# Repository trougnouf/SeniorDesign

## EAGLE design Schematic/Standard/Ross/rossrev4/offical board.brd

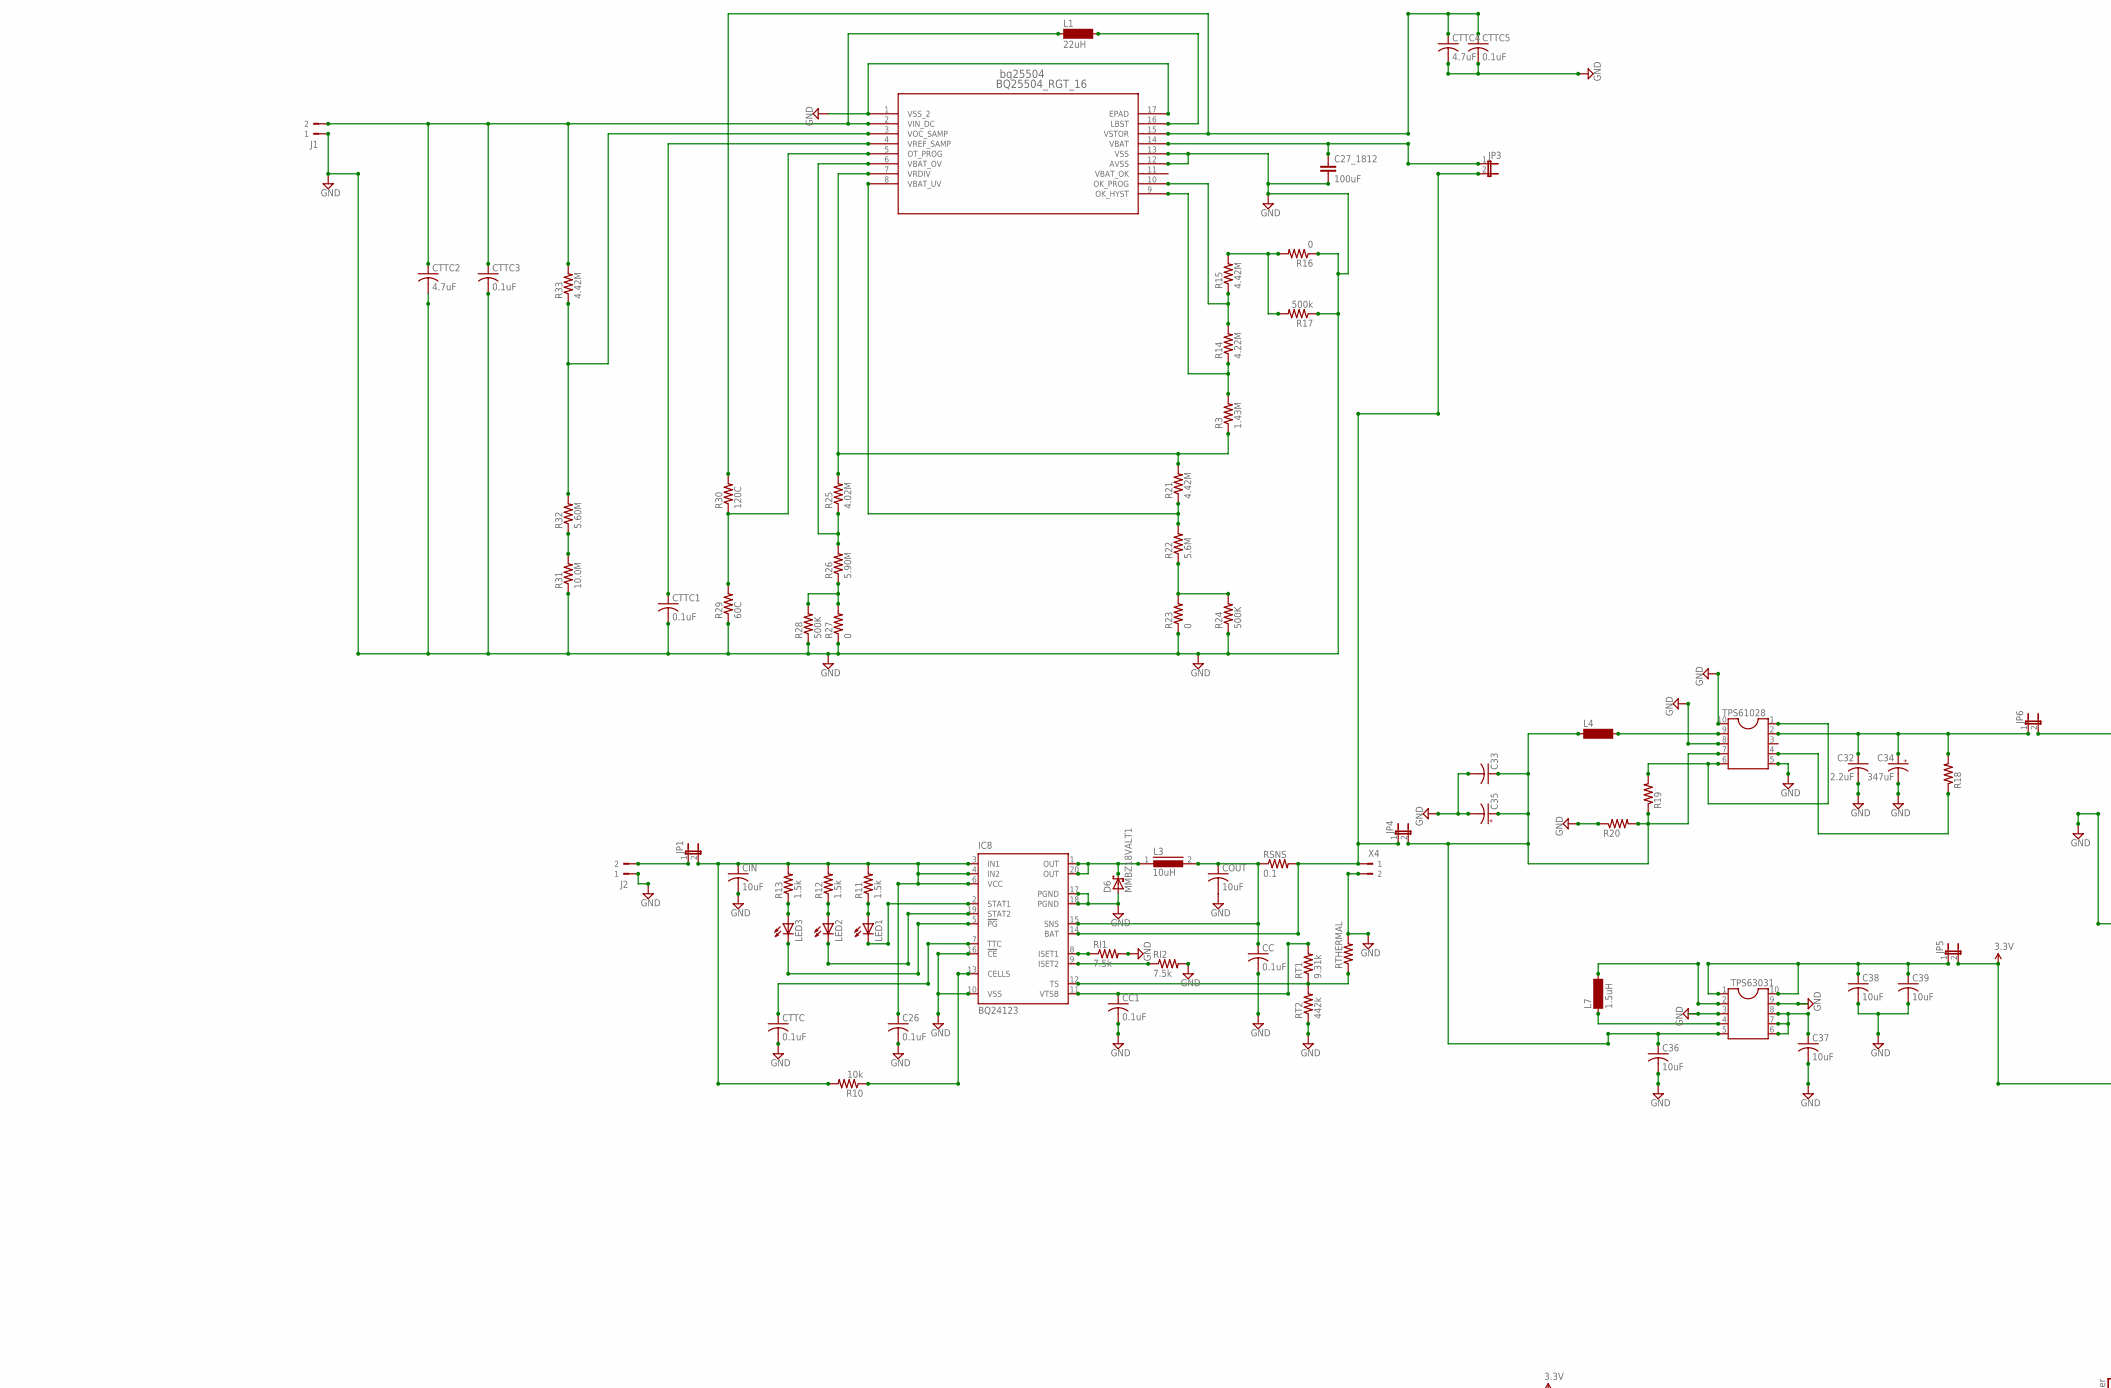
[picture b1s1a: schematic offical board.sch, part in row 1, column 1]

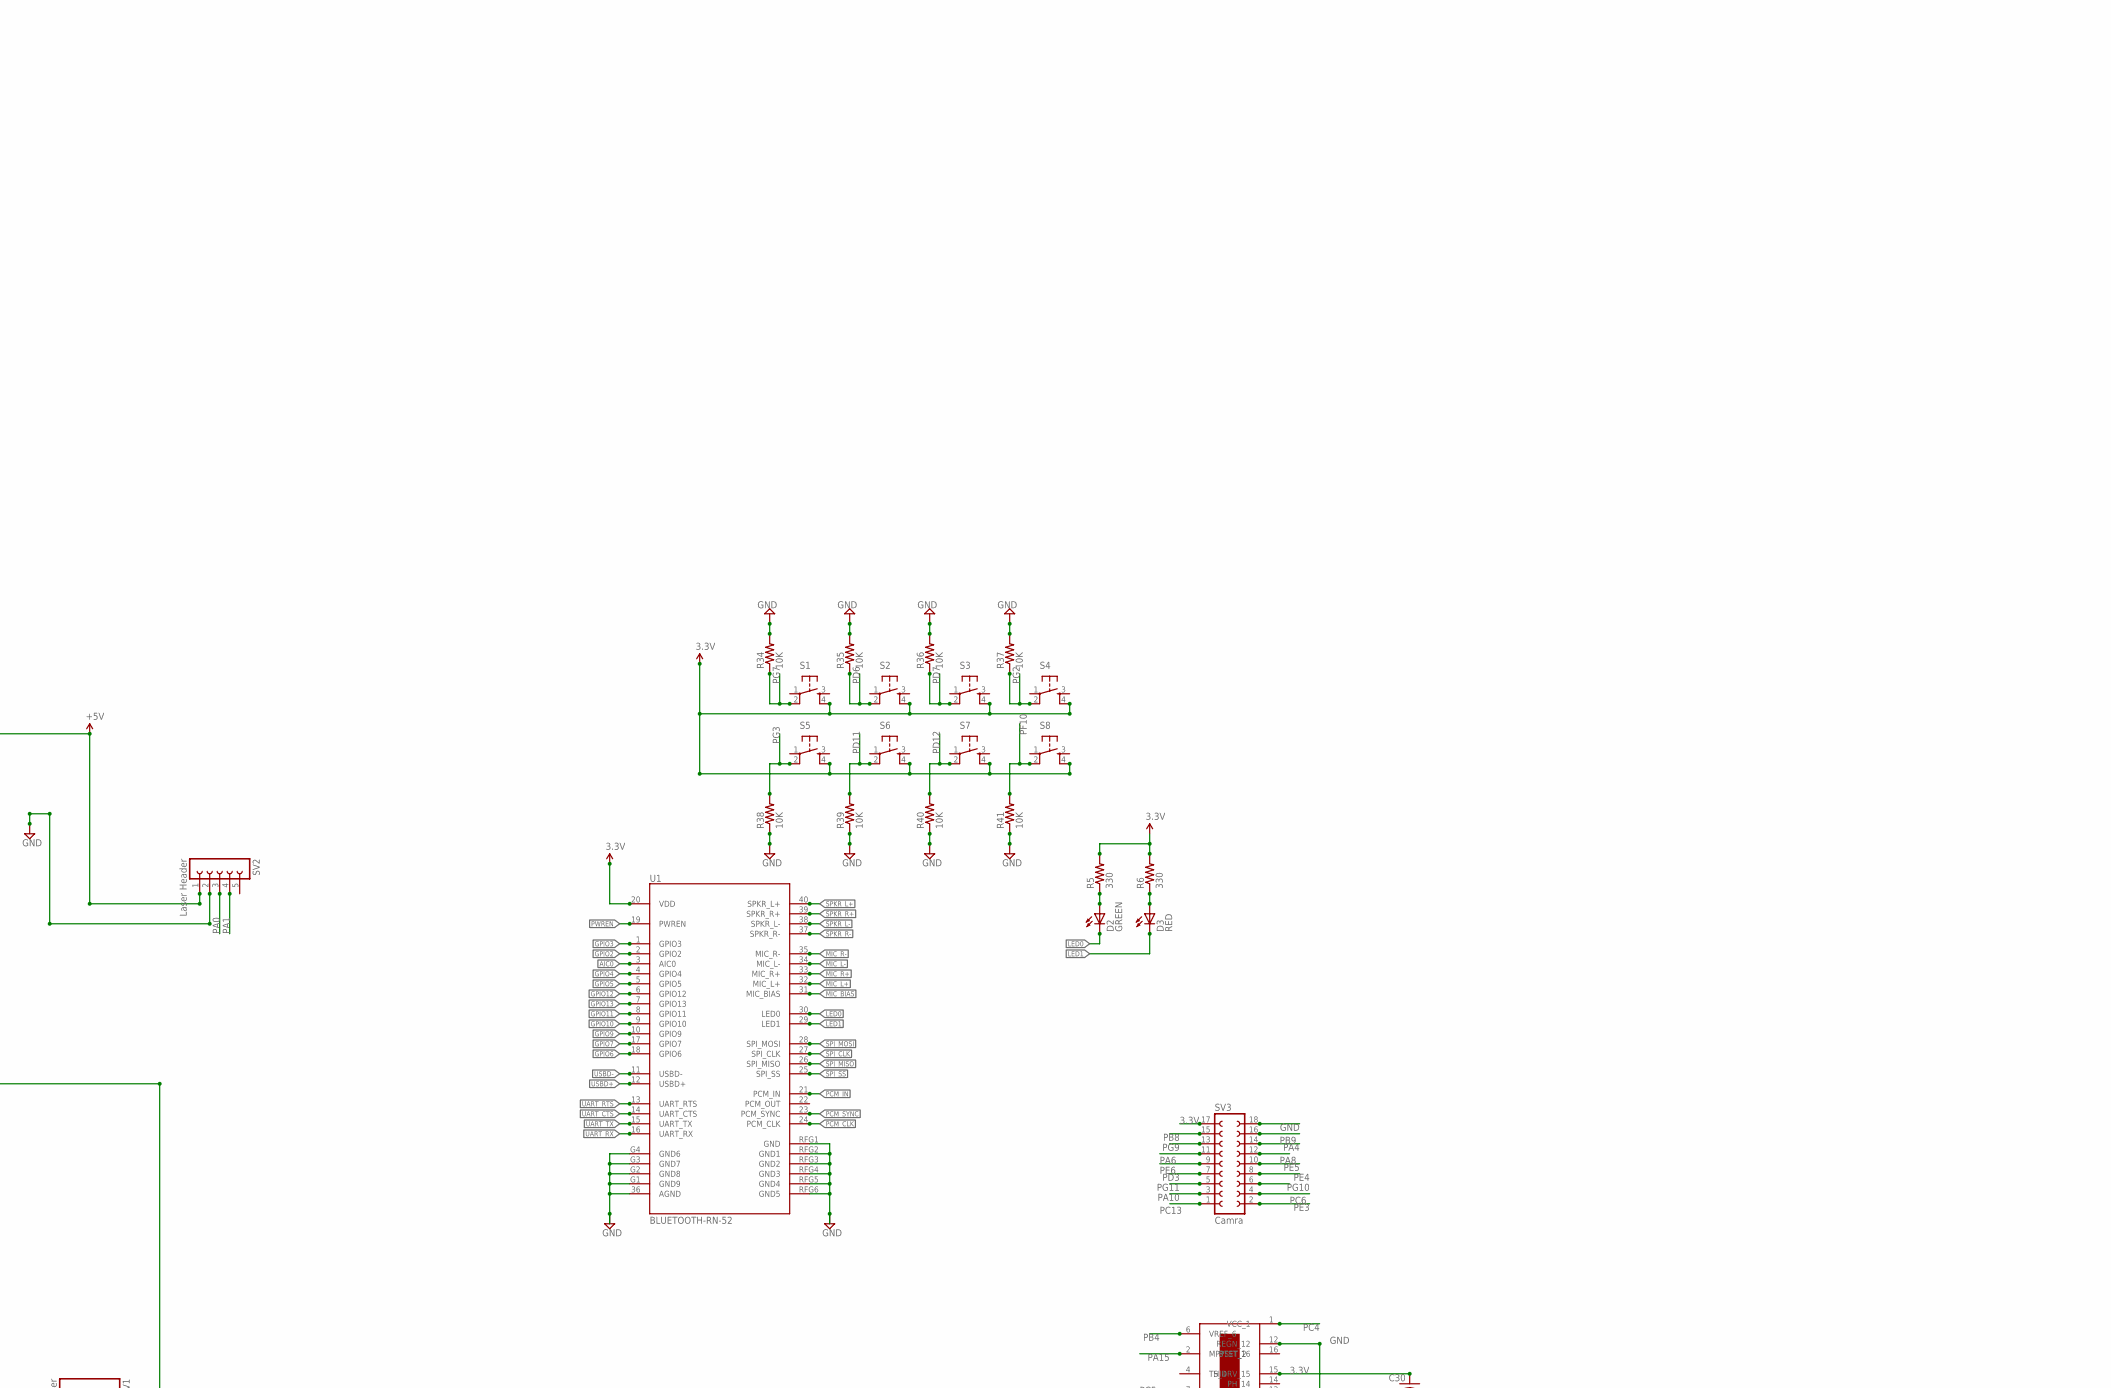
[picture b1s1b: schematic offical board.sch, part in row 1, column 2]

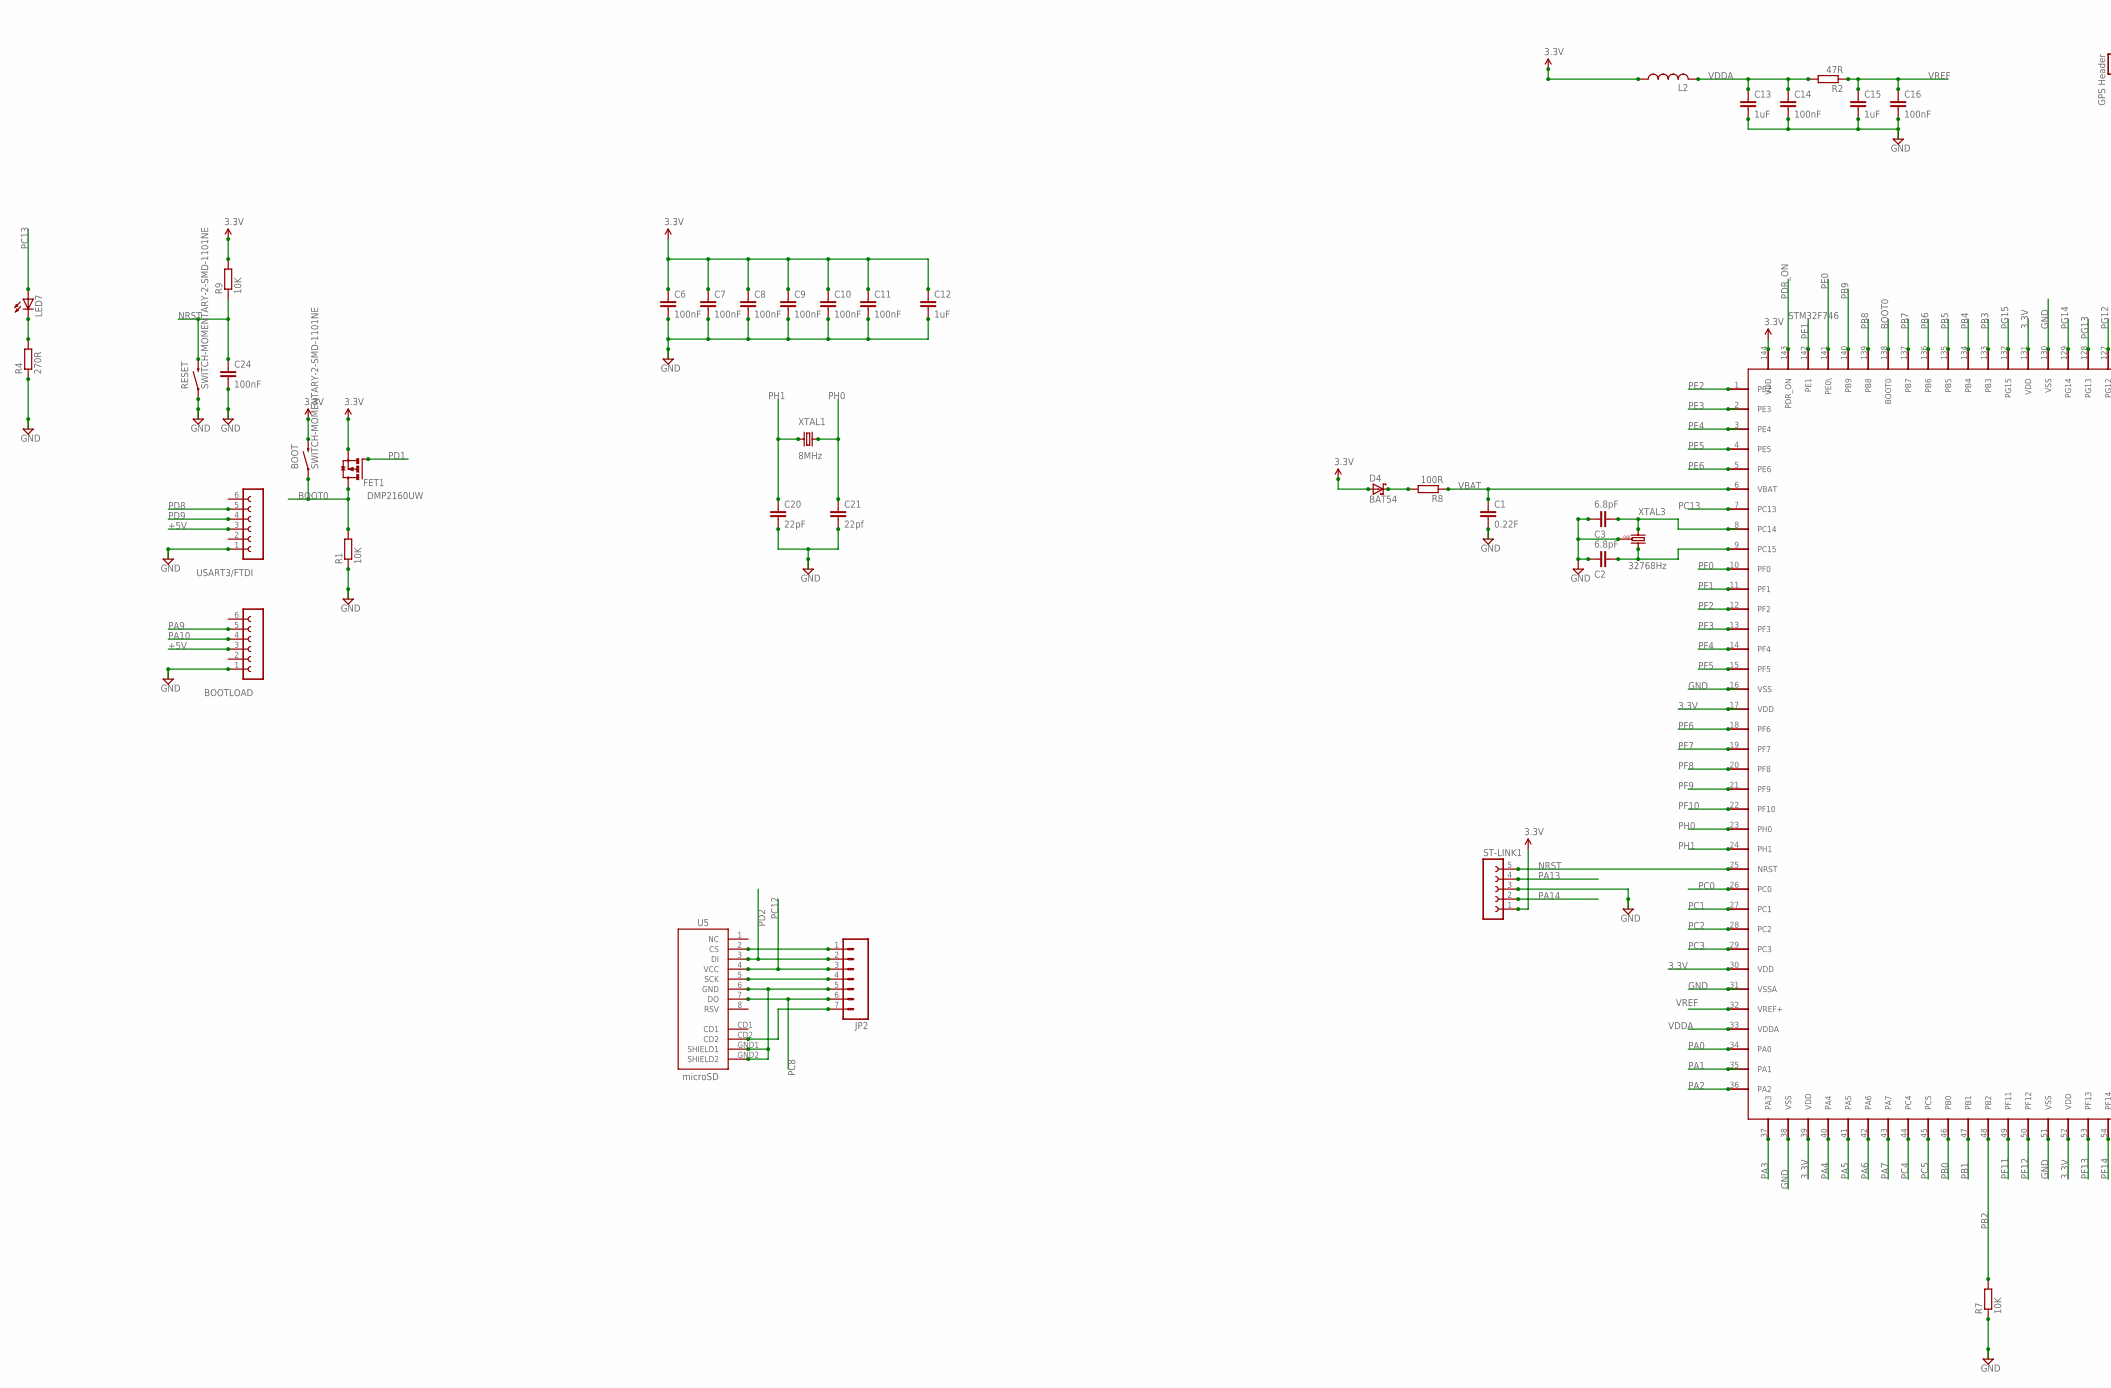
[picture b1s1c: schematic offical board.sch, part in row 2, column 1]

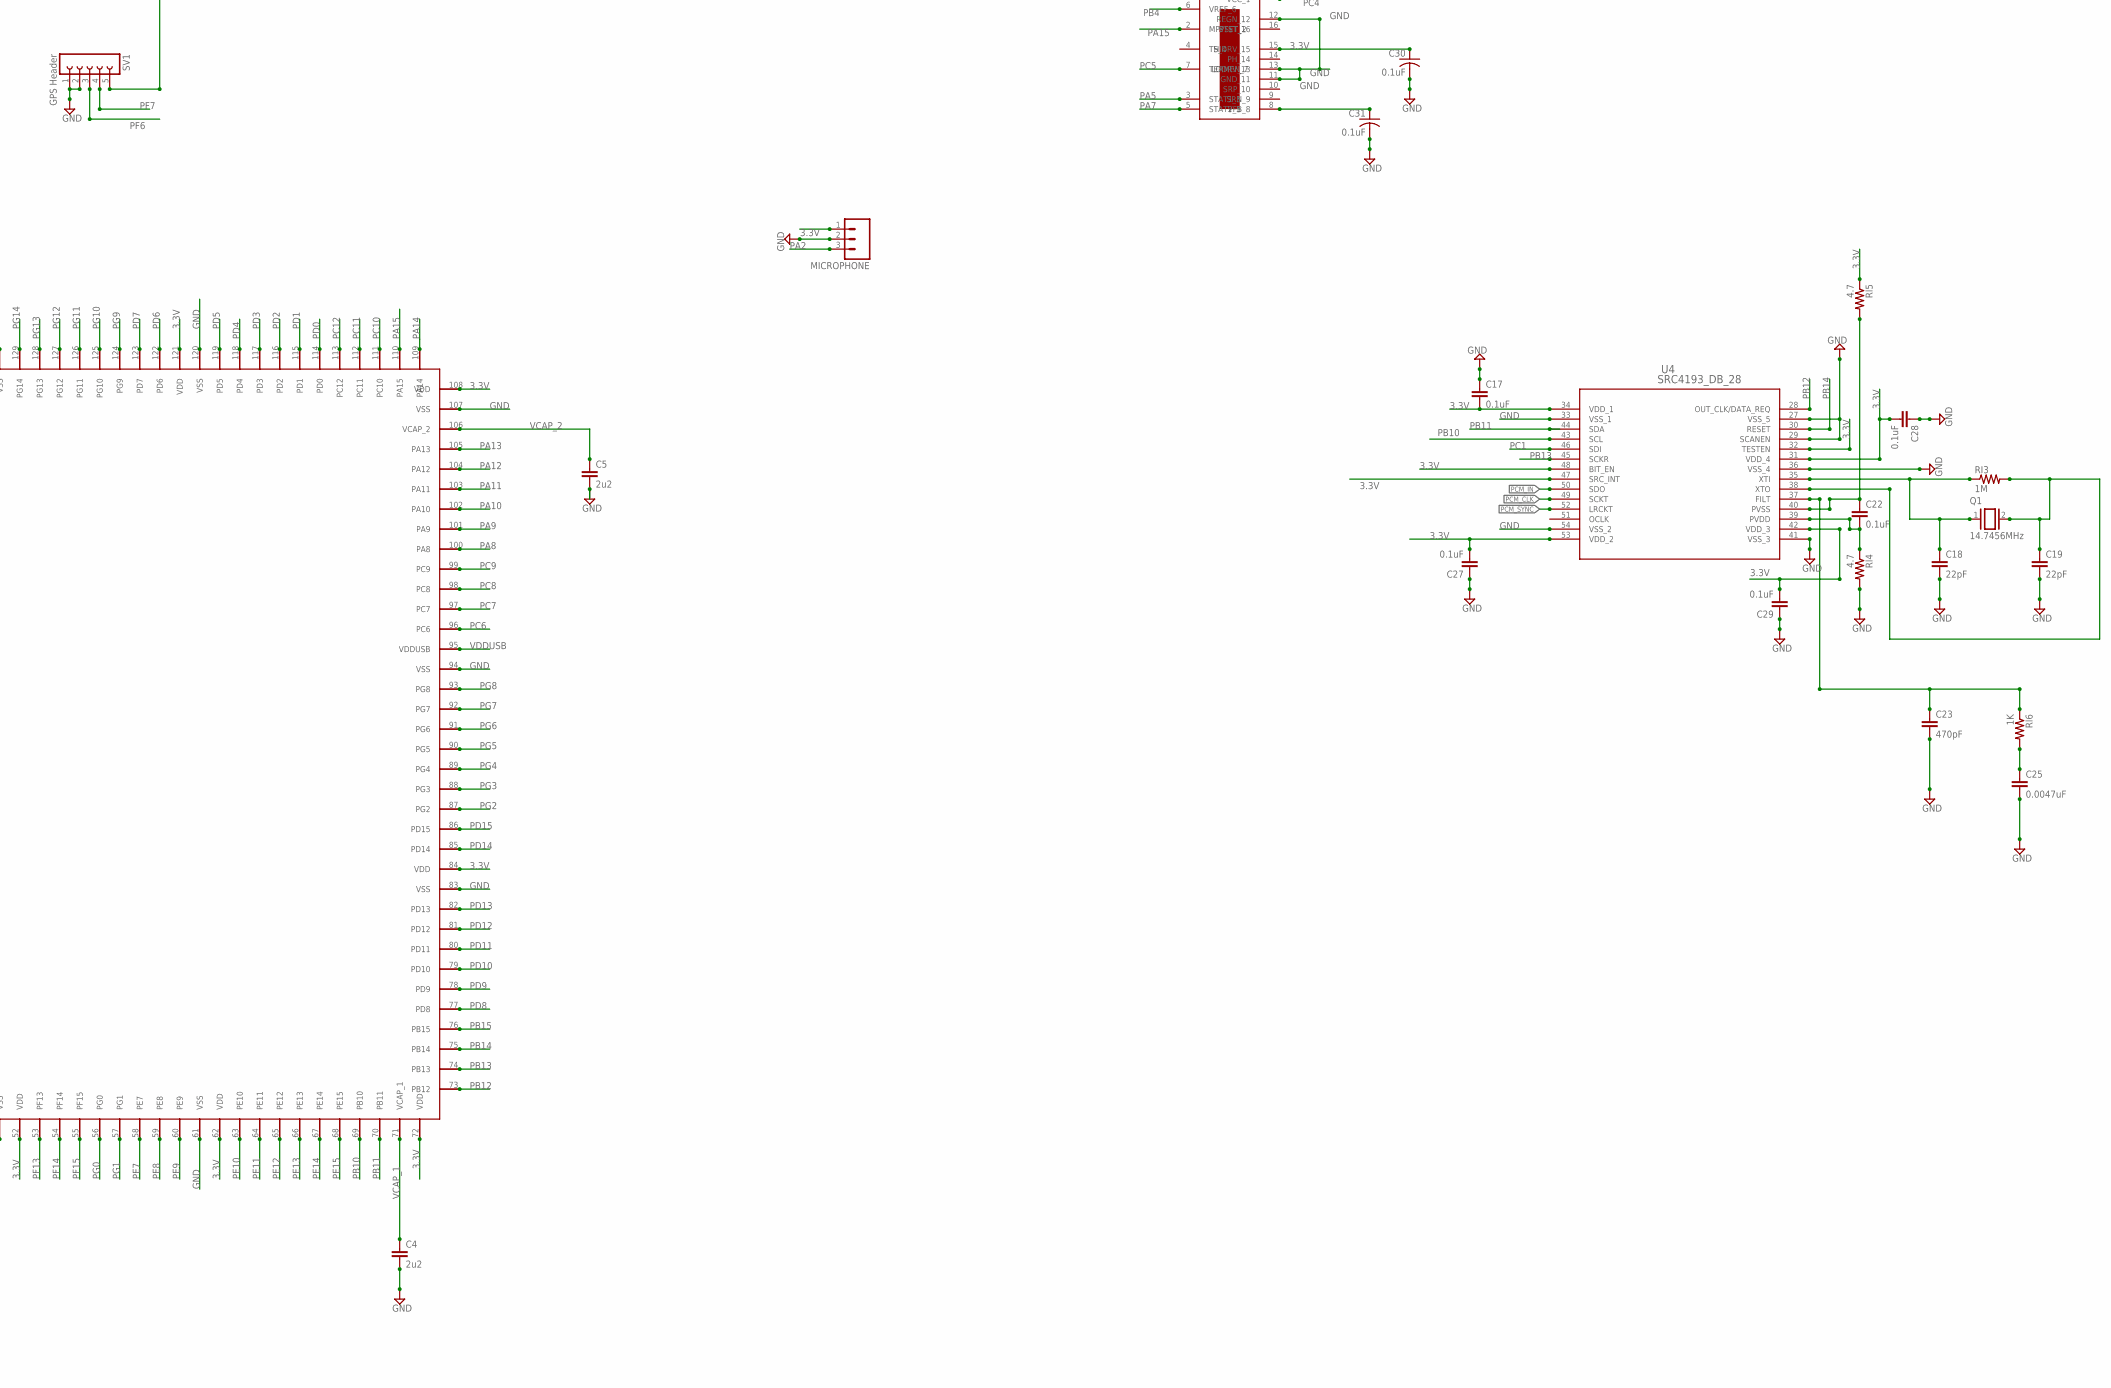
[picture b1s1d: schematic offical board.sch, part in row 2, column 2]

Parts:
BOOT: SWITCH-MOMENTARY-2-SMD-1101NE; TACTILE-SWITCH-1101NE
BOOTLOAD: FE06-1; FE06
C1: 0.22F; C5B5
C2, C3: 6.8pF; C0603
C4, C5: 2u2; C0603
C6, C7, C8, C9, C10, C11, C14, C16, C24: 100nF; C0603
C12, C13, C15: 1uF; C0603
C17, C22, C27, C28, C29, C30, C31: 0.1uF; C0603
C18, C19, C20: 22pF; C0603
C21: 22pf; C0603
C23: 470pF; C0603
C25: 0.0047uF; C0603
C26: 0.1uF; C0805
C27_1812: 100uF; C1812
C32: 2.2uF; C0603
C33: C-USC0603; C0603
C34: 347uF; 150CLZ-0810
C35: CPOL-US150CLZ-0810; 150CLZ-0810
C36, C37, C38, C39: 10uF; C0603
CC, CC1: 0.1uF; C0805
CIN: 10uF; C0805
COUT: 10uF; C0805
CTTC, CTTC1, CTTC3, CTTC5: 0.1uF; C0805
CTTC2, CTTC4: 4.7uF; C0805
D2: GREEN; LED-0603
D3: RED; LED-0603
D4: BAT54; SOT23
D6: MMBZ18VALT1; C4111-15
FET1: DMP2160UW; SUPER-SOT3
IC8: BQ24123; QFN20_3,5X4,5
J1, J2: 90-2
JP1, JP3, JP4, JP5, JP6: JP1E; JP1
JP2: M07; 1X07
L1: 22uH; SM-1206
L2: RCL_L-USL0603; RCL_L0603
L3: 10uH; DR73
L4: SM-1206
L7: 1.5uH; SM-1206
LED1, LED2, LED3: SFH482
LED7: LEDCHIP-LED0603; CHIP-LED0603
MICROPHONE: M03PTH; 1X03
Q1: 14.7456MHz; QS
R1, R7, R9: 10K; R0603
R2: 47R; R0603
R3: 1.43M; R0805
R4: 270R; R0603
R5, R6: 330; 0603-RES
R8: 100R; R0603
R10: 10k; R0805
R11, R12, R13: 1.5k; R0805
R14: 4.22M; R0805
R15, R21, R33: 4.42M; R0805
R16, R23, R27: 0; R0805
R17: 500k; R0805
R18, R19, R20: R-US_R0603; R0603
R22: 5.6M; R0805
R24, R28: 500K; R0805
R25: 4.02M; R0805
R26: 5.90M; R0805
R29: 60C; R0805
R30: 120C; R0805
R31: 10.0M; R0805
R32: 5.60M; R0805
R34, R35, R36, R37, R38, R39, R40, R41: 10K; 0603-RES
RESET: SWITCH-MOMENTARY-2-SMD-1101NE; TACTILE-SWITCH-1101NE
RI1, RI2: 7.5k; R0805
RI3: 1M; R0805
RI4, RI5: 4.7; R0805
RI6: 1K; R0805
RSNS: 0.1; R1206
RT1: 9.31k; R0805
RT2: 442k; R0805
RTHERMAL: R-US_R0805; R0805
S1, S2, S3, S4, S5, S6, S7, S8: TAC_SWITCHSMD; TACTILE_SWITCH_SMD
ST-LINK1: FE05-1
SV1: GPS Header; FE05-1
SV2: Laser Header; FE05-1
SV3: Camra; FE09-2
TPS61028, TPS63031: DIL10
U1: BLUETOOTH-RN-52; RN-52
U3: BQ25504_RGT_16; RGT16_1P7X1P7
U4: SRC4193_DB_28; DB28
U5: microSD; MICRO-SD-SOCKET-PP
U$1: STM32F746; QFN144
U$2: QFN16
USART3/FTDI: FE06-1; FE06
X4: 90-2
XTAL1: 8MHz; HC49U-V
XTAL3: 32768Hz; CRYSTAL_TC26H_3_REPAIR_SMD_SMALL_PITCH

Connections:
3.3V: BOOT.P$2 (2), C6.1, C7.1, C8.1, C9.1, C10.1, C11.1, C12.1, C17.2, C27.2, C28.2, C29.2, C30.1, D4.1 (A), FET1.2 (S), JP5.2, L2.1, MICROPHONE.1, R5.2, R6.2, R9.2, RI5.1, S1.4, S2.4, S3.4, S4.4, S5.4, S6.4, S7.4, S8.4, ST-LINK1.1, SV1.5, SV3.17, U1.20 (VDD), U4.31 (VDD_4), U4.32 (TESTEN), U4.34 (VDD_1), U4.42 (VDD_3), U4.47 (SRC_INT), U4.48 (BIT_EN), U4.53 (VDD_2), U$1.17 (VDD), U$1.30 (VDD), U$1.39 (VDD), U$1.52 (VDD), U$1.62 (VDD), U$1.72 (VDD), U$1.84 (VDD), U$1.108 (VDD), U$1.121 (VDD), U$1.131 (VDD), U$1.144 (VDD), U$2.15 (HIDRV_15)
+5V: BOOTLOAD.3, JP6.2, SV2.1, USART3/FTDI.3
AIC0: U1.3 (AIC0)
BOOT0: BOOT.P$1 (1), FET1.3 (D), R1.2, U$1.138 (BOOT0)
CD2: JP2.7, U5.CD2
CS1: JP2.1, U5.2 (CS)
GND: BOOTLOAD.1, C1.2, C2.2, C3.2, C4.2, C5.2, C6.2, C7.2, C8.2, C9.2, C10.2, C11.2, C12.2, C13.2, C14.2, C15.2, C16.2, C17.1, C18.2, C19.2, C20.2, C21.2, C23.2, C24.2, C25.2, C26.2, C27.1, C27_1812.2, C28.1, C29.1, C30.2, C31.2, C32.2, C33.2, C34.-, C35.-, C36.2, C37.2, C38.2, C39.2, CC.2, CC1.2, CIN.2, COUT.2, CTTC.2, CTTC1.2, CTTC2.2, CTTC3.2, CTTC4.2, CTTC5.2, D6.A, IC8.10 (VSS), IC8.16 (!CE), IC8.17 (PGND), IC8.18 (PGND), J1.1, J2.1, MICROPHONE.2, R1.1, R4.1, R7.1, R16.1, R17.1, R20.1, R23.1, R24.1, R27.1, R28.1, R29.1, R31.1, R34.2, R35.2, R36.2, R37.2, R38.1, R39.1, R40.1, R41.1, RESET.P$1 (1), RI1.2, RI2.2, RI4.2, RT2.1, RTHERMAL.2, ST-LINK1.3, SV1.1, SV1.2, SV2.2, SV3.18, TPS61028.5, TPS61028.8, TPS61028.10, TPS63031.3, TPS63031.9, U1.36 (AGND), U1.G1 (GND9), U1.G2 (GND8), U1.G3 (GND7), U1.G4 (GND6), U1.RFG1 (GND), U1.RFG2 (GND1), U1.RFG3 (GND2), U1.RFG4 (GND3), U1.RFG5 (GND4), U1.RFG6 (GND5), U3.1 (VSS_2), U3.12 (AVSS), U3.13 (VSS), U3.17 (EPAD), U4.27 (VSS_5), U4.29 (SCANEN), U4.33 (VSS_1), U4.36 (VSS_4), U4.41 (VSS_3), U4.54 (VSS_2), U$1.16 (VSS), U$1.31 (VSSA), U$1.38 (VSS), U$1.51 (VSS), U$1.61 (VSS), U$1.83 (VSS), U$1.94 (VSS), U$1.107 (VSS), U$1.120 (VSS), U$1.130 (VSS), U$2.11 (GND_11), U$2.12 (REGN_12), U$2.13 (LODRV_13), USART3/FTDI.1, X4.2, XTAL3.GND
GND2: JP2.5, U5.6 (GND), U5.GND1 (SHIELD1), U5.GND2 (SHIELD2)
GPIO2: U1.2 (GPIO2)
GPIO3: U1.1 (GPIO3)
GPIO4: U1.4 (GPIO4)
GPIO5: U1.5 (GPIO5)
GPIO6: U1.18 (GPIO6)
GPIO7: U1.17 (GPIO7)
GPIO9: U1.10 (GPIO9)
GPIO10: U1.9 (GPIO10)
GPIO11: U1.8 (GPIO11)
GPIO12: U1.6 (GPIO12)
GPIO13: U1.7 (GPIO13)
LED0: D2.C, U1.30 (LED0)
LED1: D3.C, U1.29 (LED1)
MIC_BIAS: U1.31 (MIC_BIAS)
MIC_L+: U1.32 (MIC_L+)
MIC_L-: U1.34 (MIC_L-)
MIC_R+: U1.33 (MIC_R+)
MIC_R-: U1.35 (MIC_R-)
unnamed: D3.A, R6.1
unnamed: D2.A, R5.1
unnamed: D4.3 (C), R8.2
unnamed: C33.1, C35.+, C36.1, JP4.2, L4.1, R19.1, R20.2, TPS61028.7, TPS63031.5
unnamed: C18.1, Q1.1, RI3.1, U4.35 (XTI)
unnamed: D6.C, IC8.1 (OUT), IC8.20 (OUT), L3.1
unnamed: C23.1, RI6.1, U4.37 (FILT)
unnamed: J2.2, JP1.1
unnamed: C19.1, Q1.2, RI3.2, U4.38 (XTO)
unnamed: CTTC2.1, CTTC3.1, J1.2, L1.1, R33.2, U3.2 (VIN_DC)
unnamed: C25.1, RI6.2
unnamed: CC.1, COUT.1, IC8.15 (SNS), L3.2, RSNS.1
unnamed: C22.2, RI4.1, U4.39 (PVDD)
unnamed: C22.1, RI5.2, U4.40 (PVSS)
unnamed: C27_1812.1, JP3.1, U3.14 (VBAT)
unnamed: CTTC4.1, CTTC5.1, R30.2, U3.15 (VSTOR)
unnamed: IC8.14 (BAT), JP3.2, JP4.1, RSNS.2, X4.1
unnamed: IC8.8 (ISET1), RI1.1
unnamed: R14.2, R15.1, U3.10 (OK_PROG)
unnamed: R3.2, R14.1, U3.9 (OK_HYST)
unnamed: IC8.9 (ISET2), RI2.1
unnamed: IC8.12 (TS), RT1.1, RT2.2, RTHERMAL.1
unnamed: CC1.1, IC8.11 (VTSB), RT1.2
unnamed: LED3.A, R13.1
unnamed: LED2.A, R12.1
unnamed: LED1.A, R11.1
unnamed: IC8.2 (STAT1), LED1.K (C)
unnamed: IC8.19 (STAT2), LED2.K (C)
unnamed: IC8.5 (!PG), LED3.K (C)
unnamed: CTTC.1, IC8.7 (TTC)
unnamed: IC8.13 (CELLS), R10.1
unnamed: R15.2, R16.2, R17.2
unnamed: R3.1, R21.2, R25.2, U3.7 (VRDIV)
unnamed: R21.1, R22.2, U3.8 (VBAT_UV)
unnamed: R22.1, R23.2, R24.2
unnamed: C38.1, C39.1, JP5.1, TPS63031.1, TPS63031.10
unnamed: C26.1, CIN.1, IC8.3 (IN1), IC8.4 (IN2), IC8.6 (VCC), JP1.2, R10.2, R11.2, R12.2, R13.2
unnamed: C31.1, U$2.8 (VFB_8)
unnamed: L1.2, U3.16 (LBST)
unnamed: R25.1, R26.2, U3.6 (VBAT_OV)
unnamed: R26.1, R27.2, R28.2
unnamed: CTTC1.1, U3.4 (VREF_SAMP)
unnamed: C32.1, C34.+, JP6.1, R18.2, TPS61028.2
unnamed: R18.1, TPS61028.4
unnamed: R19.2, TPS61028.1, TPS61028.6
unnamed: R29.2, R30.1, U3.5 (OT_PROG)
unnamed: L4.2, TPS61028.9
unnamed: L7.2, TPS63031.2
unnamed: L7.1, TPS63031.4
unnamed: C37.1, TPS63031.6, TPS63031.7, TPS63031.8
unnamed: R31.2, R32.1
unnamed: R32.2, R33.1, U3.3 (VOC_SAMP)
unnamed: LED7.C, R4.2
NRST: C24.1, R9.1, RESET.P$2 (2), ST-LINK1.5, U$1.25 (NRST)
PA0: SV2.3, U$1.34 (PA0)
PA1: SV2.4, U$1.35 (PA1)
PA2: MICROPHONE.3, U$1.36 (PA2)
PA3: U$1.37 (PA3)
PA4: SV3.14, U$1.40 (PA4)
PA5: U$1.41 (PA5), U$2.3 (STAT1_3)
PA6: SV3.11, U$1.42 (PA6)
PA7: U$1.43 (PA7), U$2.5 (STAT2_5)
PA8: SV3.12, U$1.100 (PA8)
PA9: BOOTLOAD.5, U$1.101 (PA9)
PA10: BOOTLOAD.4, SV3.3, U$1.102 (PA10)
PA11: U$1.103 (PA11)
PA12: U$1.104 (PA12)
PA13: ST-LINK1.4, U$1.105 (PA13)
PA14: ST-LINK1.2, U$1.109 (PA14)
PA15: U$1.110 (PA15), U$2.2 (MPPSET_2)
PB0: U$1.46 (PB0)
PB1: U$1.47 (PB1)
PB2: R7.2, U$1.48 (PB2)
PB3: U$1.133 (PB3)
PB4: U$1.134 (PB4), U$2.6 (VREF_6)
PB5: U$1.135 (PB5)
PB6: U$1.136 (PB6)
PB7: U$1.137 (PB7)
PB8: SV3.15, U$1.139 (PB8)
PB9: SV3.16, U$1.140 (PB9)
PB10: U4.43 (SCL), U$1.69 (PB10)
PB11: U4.44 (SDA), U$1.70 (PB11)
PB12: U4.28 (OUT_CLK/DATA_REQ), U$1.73 (PB12)
PB13: U4.45 (SCKR), U$1.74 (PB13)
PB14: U4.30 (RESET), U$1.75 (PB14)
PB15: U$1.76 (PB15)
PC0: U$1.26 (PC0)
PC1: U4.46 (SDI), U$1.27 (PC1)
PC2: U$1.28 (PC2)
PC3: U$1.29 (PC3)
PC4: U$1.44 (PC4), U$2.1 (VCC_1)
PC5: U$1.45 (PC5), U$2.7 (TERMEN_7)
PC6: SV3.4, U$1.96 (PC6)
PC7: U$1.97 (PC7)
PC8: JP2.6, U5.7 (DO), U$1.98 (PC8)
PC9: U$1.99 (PC9)
PC10: U$1.111 (PC10)
PC11: U$1.112 (PC11)
PC12: JP2.3, U5.4 (VCC), U$1.113 (PC12)
PC13: LED7.A, SV3.1, U$1.7 (PC13)
PC14: C3.1, U$1.8 (PC14), XTAL3.1
PC15: C2.1, U$1.9 (PC15), XTAL3.2
PCM_CLK: U1.24 (PCM_CLK), U4.49 (SCKT)
PCM_IN: U1.21 (PCM_IN), U4.50 (SDO)
PCM_SYNC: U1.23 (PCM_SYNC), U4.52 (LRCKT)
PD0: U$1.114 (PD0)
PD1: FET1.1 (G), U$1.115 (PD1)
PD2: JP2.2, U5.3 (DI), U$1.116 (PD2)
PD3: SV3.7, U$1.117 (PD3)
PD4: U$1.118 (PD4)
PD5: U$1.119 (PD5)
PD6: R35.1, S2.2, U$1.122 (PD6)
PD7: R36.1, S3.2, U$1.123 (PD7)
PD8: U$1.77 (PD8), USART3/FTDI.5
PD9: U$1.78 (PD9), USART3/FTDI.4
PD10: U$1.79 (PD10)
PD11: R39.2, S6.2, U$1.80 (PD11)
PD12: R40.2, S7.2, U$1.81 (PD12)
PD13: U$1.82 (PD13)
PD14: U$1.85 (PD14)
PD15: U$1.86 (PD15)
PDR_ON: U$1.143 (PDR_ON)
PE0: U$1.141 (PE0\)
PE1: U$1.142 (PE1)
PE2: U$1.1 (PE2)
PE3: SV3.2, U$1.2 (PE3)
PE4: SV3.8, U$1.3 (PE4)
PE5: SV3.10, U$1.4 (PE5)
PE6: SV3.9, U$1.5 (PE6)
PE7: U$1.58 (PE7)
PE8: U$1.59 (PE8)
PE9: U$1.60 (PE9)
PE10: U$1.63 (PE10)
PE11: U$1.64 (PE11)
PE12: U$1.65 (PE12)
PE13: U$1.66 (PE13)
PE14: U$1.67 (PE14)
PE15: U$1.68 (PE15)
PF0: U$1.10 (PF0)
PF1: U$1.11 (PF1)
PF2: U$1.12 (PF2)
PF3: U$1.13 (PF3)
PF4: U$1.14 (PF4)
PF5: U$1.15 (PF5)
PF6: SV1.3, U$1.18 (PF6)
PF7: SV1.4, U$1.19 (PF7)
PF8: U$1.20 (PF8)
PF9: U$1.21 (PF9)
PF10: R41.2, S8.2, U$1.22 (PF10)
PF11: U$1.49 (PF11)
PF12: U$1.50 (PF12)
PF13: U$1.53 (PF13)
PF14: U$1.54 (PF14)
PF15: U$1.55 (PF15)
PG0: U$1.56 (PG0)
PG1: U$1.57 (PG1)
PG2: R37.1, S4.2, U$1.87 (PG2)
PG3: R38.2, S5.2, U$1.88 (PG3)
PG4: U$1.89 (PG4)
PG5: U$1.90 (PG5)
PG6: U$1.91 (PG6)
PG7: R34.1, S1.2, U$1.92 (PG7)
PG8: U$1.93 (PG8)
PG9: SV3.13, U$1.124 (PG9)
PG10: SV3.6, U$1.125 (PG10)
PG11: SV3.5, U$1.126 (PG11)
PG12: U$1.127 (PG12)
PG13: U$1.128 (PG13)
PG14: U$1.129 (PG14)
PG15: U$1.132 (PG15)
PH0: C21.1, U$1.23 (PH0), XTAL1.2
PH1: C20.1, U$1.24 (PH1), XTAL1.1
PWREN: U1.19 (PWREN)
SCK1: JP2.4, U5.5 (SCK)
SPI_CLK: U1.27 (SPI_CLK)
SPI_MISO: U1.26 (SPI_MISO)
SPI_MOSI: U1.28 (SPI_MOSI)
SPI_SS: U1.25 (SPI_SS)
SPKR_L+: U1.40 (SPKR_L+)
SPKR_L-: U1.38 (SPKR_L-)
SPKR_R+: U1.39 (SPKR_R+)
SPKR_R-: U1.37 (SPKR_R-)
UART_CTS: U1.14 (UART_CTS)
UART_RTS: U1.13 (UART_RTS)
UART_RX: U1.16 (UART_RX)
UART_TX: U1.15 (UART_TX)
USBD+: U1.12 (USBD+)
USBD-: U1.11 (USBD-)
VBAT: C1.1, R8.1, U$1.6 (VBAT)
VCAP_1: C4.1, U$1.71 (VCAP_1)
VCAP_2: C5.1, U$1.106 (VCAP_2)
VDDA: C13.1, C14.1, L2.2, R2.2, U$1.33 (VDDA)
VDDUSB: U$1.95 (VDDUSB)
VREF: C15.1, C16.1, R2.1, U$1.32 (VREF+)

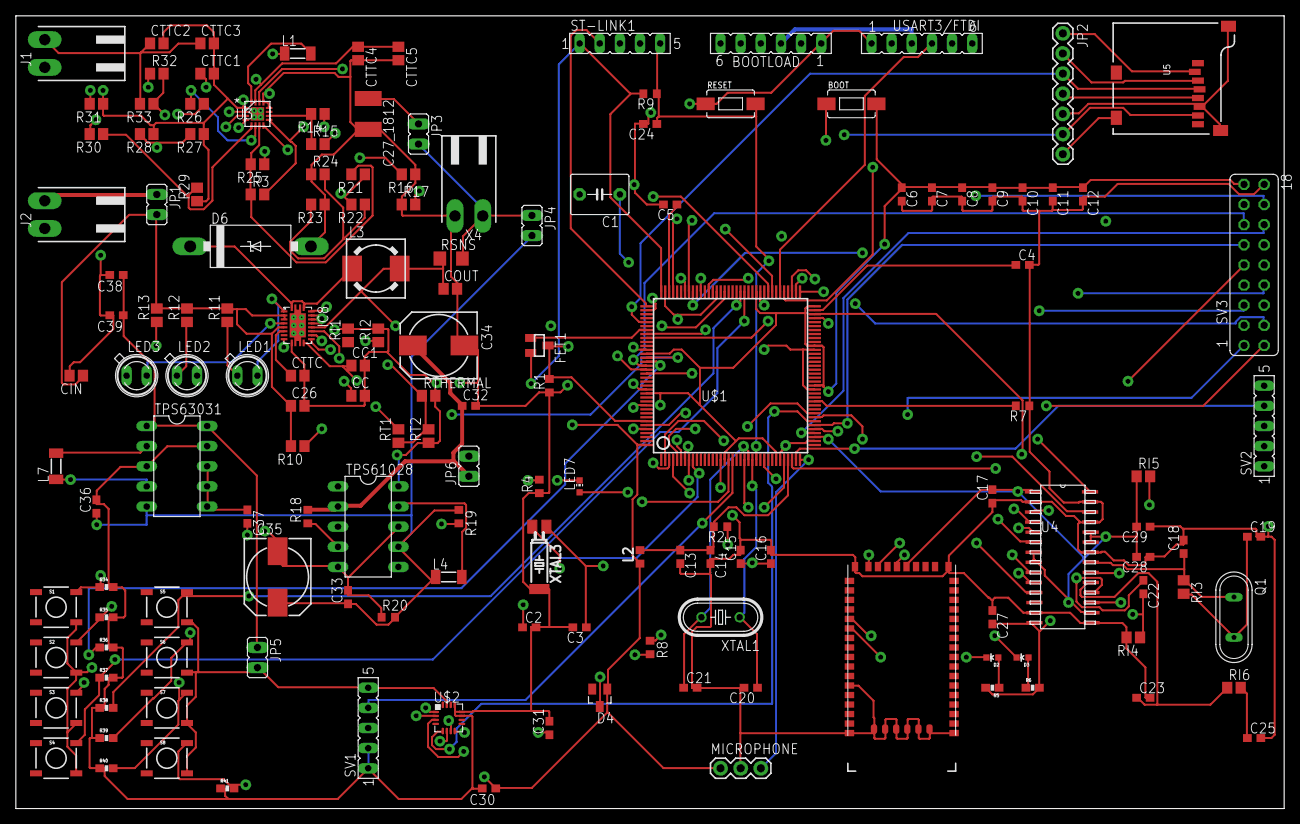
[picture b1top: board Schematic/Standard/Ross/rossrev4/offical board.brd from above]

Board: 4 copper layers, 160.0 x 100.0 mm, 153 parts (0 on the bottom side), 127 nets.

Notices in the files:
parts and their libraries:
SparkFun-Electromechanical: Licensing: Creative Commons ShareAlike 4.0 International - https://creativecommons.org/licenses/by-sa/4.0
SparkFun-RF: Licensing: CC v3.0 Share-Alike You are welcome to use this library for commercial purposes.
